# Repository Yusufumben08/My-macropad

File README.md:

# My-macropad

first electronics project. I found this last second so i couldnt do much more than this because of the time constraint. Made in 5~ hours. I have access to a 3d printer and will print the case myself (possibly iterating on it to make it look better.)

Parts list / BOM: <br>
*Seeed XIAO RP2040 1x505TL [link](https://www.robotsepeti.com/xiao-rp2040-rpi-tabanli-gelistirme-karti?srsltid=AfmBOoo-r4c254mQOyLpYBEuEKQ4UjQO35CaTtn0vQ_AmNtM1wtQWy1J) <br>
*9x MX-Style switches 450-500TL (this was the only listing i found and it sells 10 so price is approximated.) [link](https://www.hepsiburada.com/cherry-mx-mekanik-klavye-blue-switch-yedek-tus-10-adet-pm-HB00000TWEHL). <br>
*EC11 Rotary encoder 1x32TL [link](https://www.robolinkmarket.com/rotary-encoder-ec11-switch-20mm?srsltid=AfmBOople9BYicgfWd3Uo1zGUX4RngiUt7oklPvnFAZ-H85KapwNfm2Q)<br>
*9x Blank DSA keycaps (wasnt able to find a listing on this one, i can source it myself when i find it.)<br>
*9x SK6812 MINI-E LEDs 35TL~ (same with the switches, the only listing i could find sold 10 so approximate price.) [link](https://tr.aliexpress.com/item/1005005248164351.html) <br>
*9x Through-hole 1N4148 Diodes 9x0,41 ,3,67TL [link](https://www.direnc.net/1n4148-diyot-mic)<br>

Total: 1025TL~ = 24~ US dollars

Schematic:

PCB Image:

Model of assembled form:

Case Parts:

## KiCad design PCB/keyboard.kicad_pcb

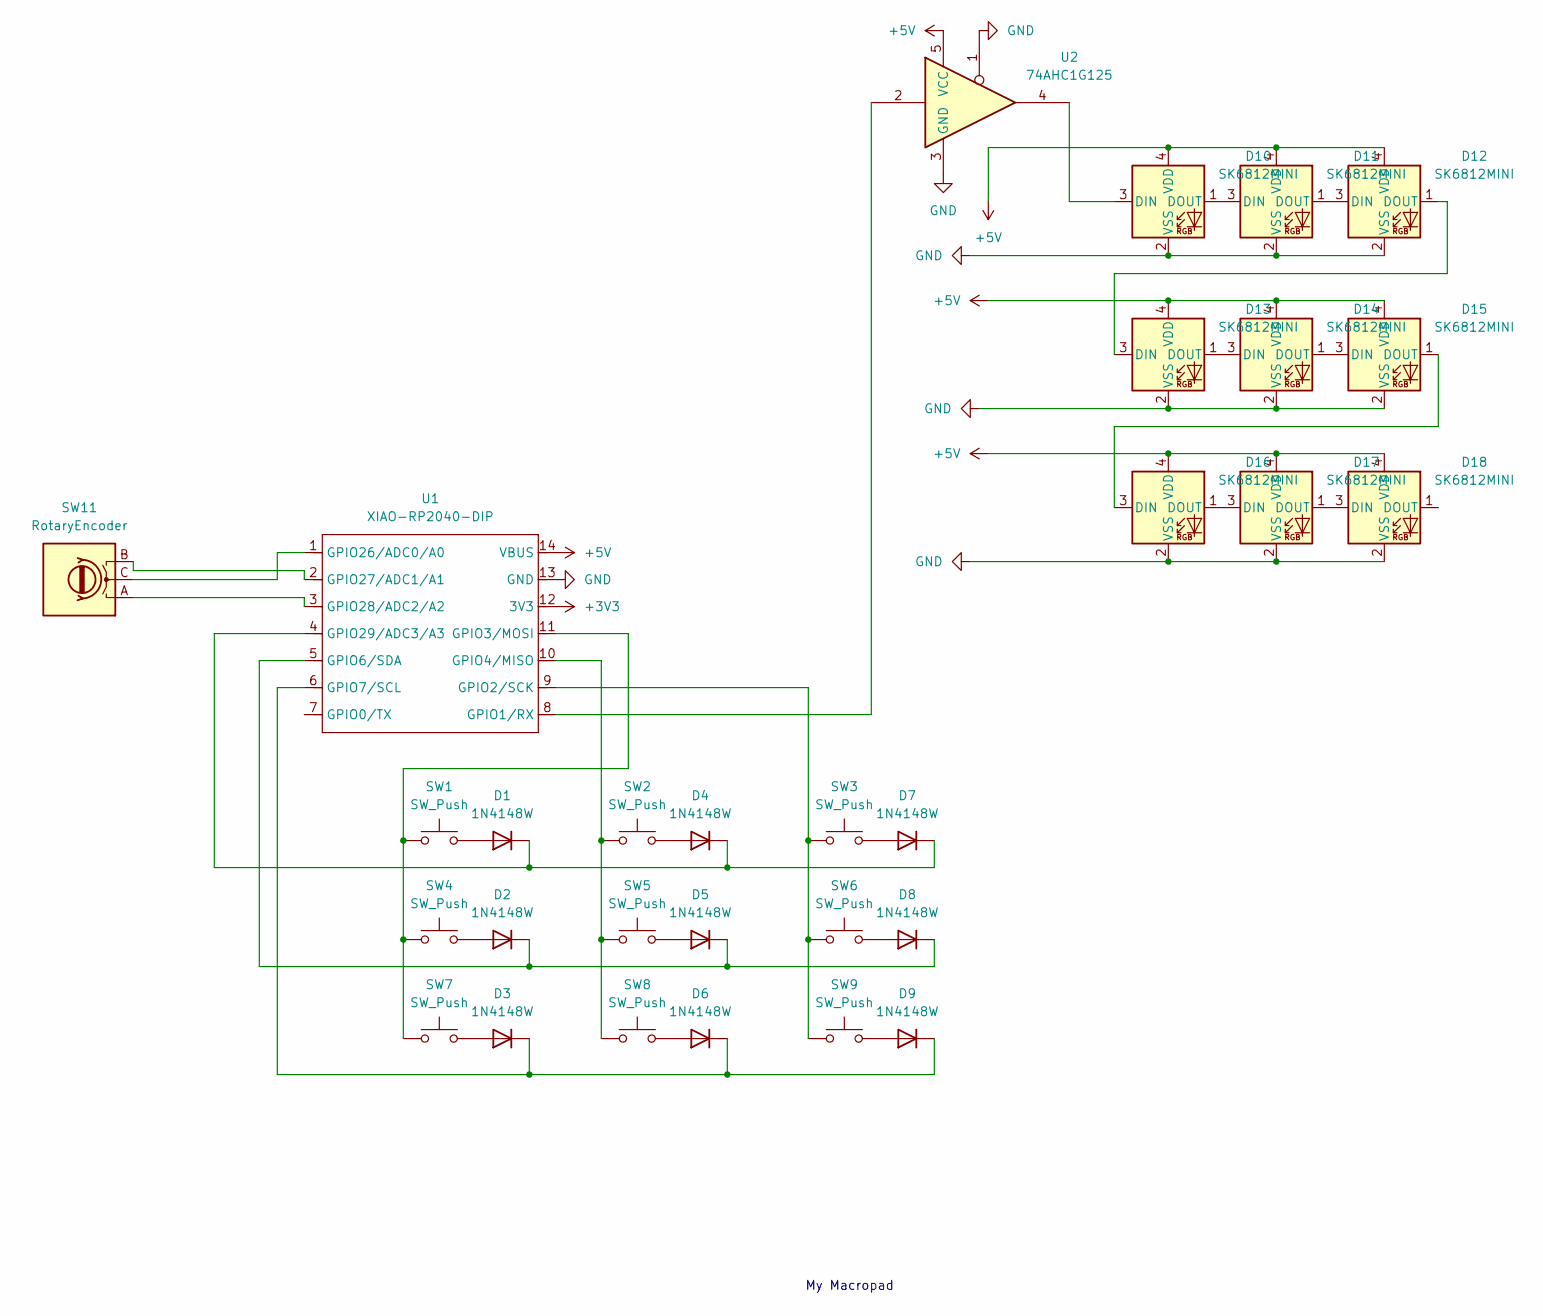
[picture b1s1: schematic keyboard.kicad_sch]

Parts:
D1, D2, D3, D4, D5, D6, D7, D8, D9: 1N4148W; D_SOD-123
D10, D11, D12, D13, D14, D15, D16, D17, D18: SK6812MINI; LED_SK6812MINI_PLCC4_3.5x3.5mm_P1.75mm
SW1, SW2, SW3, SW4, SW5, SW6, SW7, SW8, SW9: SW_Push; SW_Cherry_MX_1.00u_PCB
SW11: RotaryEncoder; RotaryEncoder_Alps_EC11E-Switch_Vertical_H20mm
U1: XIAO-RP2040-DIP
U2: 74AHC1G125; SOT95P280X140-5N

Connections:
+3V3: U1.12 (3V3)
+5V: D10.4 (VDD), D11.4 (VDD), D12.4 (VDD), D13.4 (VDD), D14.4 (VDD), D15.4 (VDD), D16.4 (VDD), D17.4 (VDD), D18.4 (VDD), U1.14 (VBUS), U2.5 (VCC)
GND: D10.2 (VSS), D11.2 (VSS), D12.2 (VSS), D13.2 (VSS), D14.2 (VSS), D15.2 (VSS), D16.2 (VSS), D17.2 (VSS), D18.2 (VSS), U1.13 (GND), U2.1, U2.3 (GND)
unnamed: D1.2 (A), SW1.2
unnamed: D1.1 (K), D4.1 (K), D7.1 (K), U1.4 (GPIO29/ADC3/A3)
unnamed: D2.2 (A), SW4.2
unnamed: D2.1 (K), D5.1 (K), D8.1 (K), U1.5 (GPIO6/SDA)
unnamed: D3.2 (A), SW7.2
unnamed: D3.1 (K), D6.1 (K), D9.1 (K), U1.6 (GPIO7/SCL)
unnamed: D4.2 (A), SW2.2
unnamed: D5.2 (A), SW5.2
unnamed: D6.2 (A), SW8.2
unnamed: D7.2 (A), SW3.2
unnamed: D8.2 (A), SW6.2
unnamed: D9.2 (A), SW9.2
unnamed: D10.3 (DIN), U2.4
unnamed: D10.1 (DOUT), D11.3 (DIN)
unnamed: D11.1 (DOUT), D12.3 (DIN)
unnamed: D12.1 (DOUT), D13.3 (DIN)
unnamed: D13.1 (DOUT), D14.3 (DIN)
unnamed: D14.1 (DOUT), D15.3 (DIN)
unnamed: D15.1 (DOUT), D16.3 (DIN)
unnamed: D16.1 (DOUT), D17.3 (DIN)
unnamed: D17.1 (DOUT), D18.3 (DIN)
unnamed: U1.8 (GPIO1/RX), U2.2
unnamed: SW3.1, SW6.1, SW9.1, U1.9 (GPIO2/SCK)
unnamed: SW1.1, SW4.1, SW7.1, U1.11 (GPIO3/MOSI)
unnamed: SW2.1, SW5.1, SW8.1, U1.10 (GPIO4/MISO)
unnamed: SW11.C, U1.1 (GPIO26/ADC0/A0)
unnamed: SW11.B, U1.2 (GPIO27/ADC1/A1)
unnamed: SW11.A, U1.3 (GPIO28/ADC2/A2)

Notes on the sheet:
My Macropad

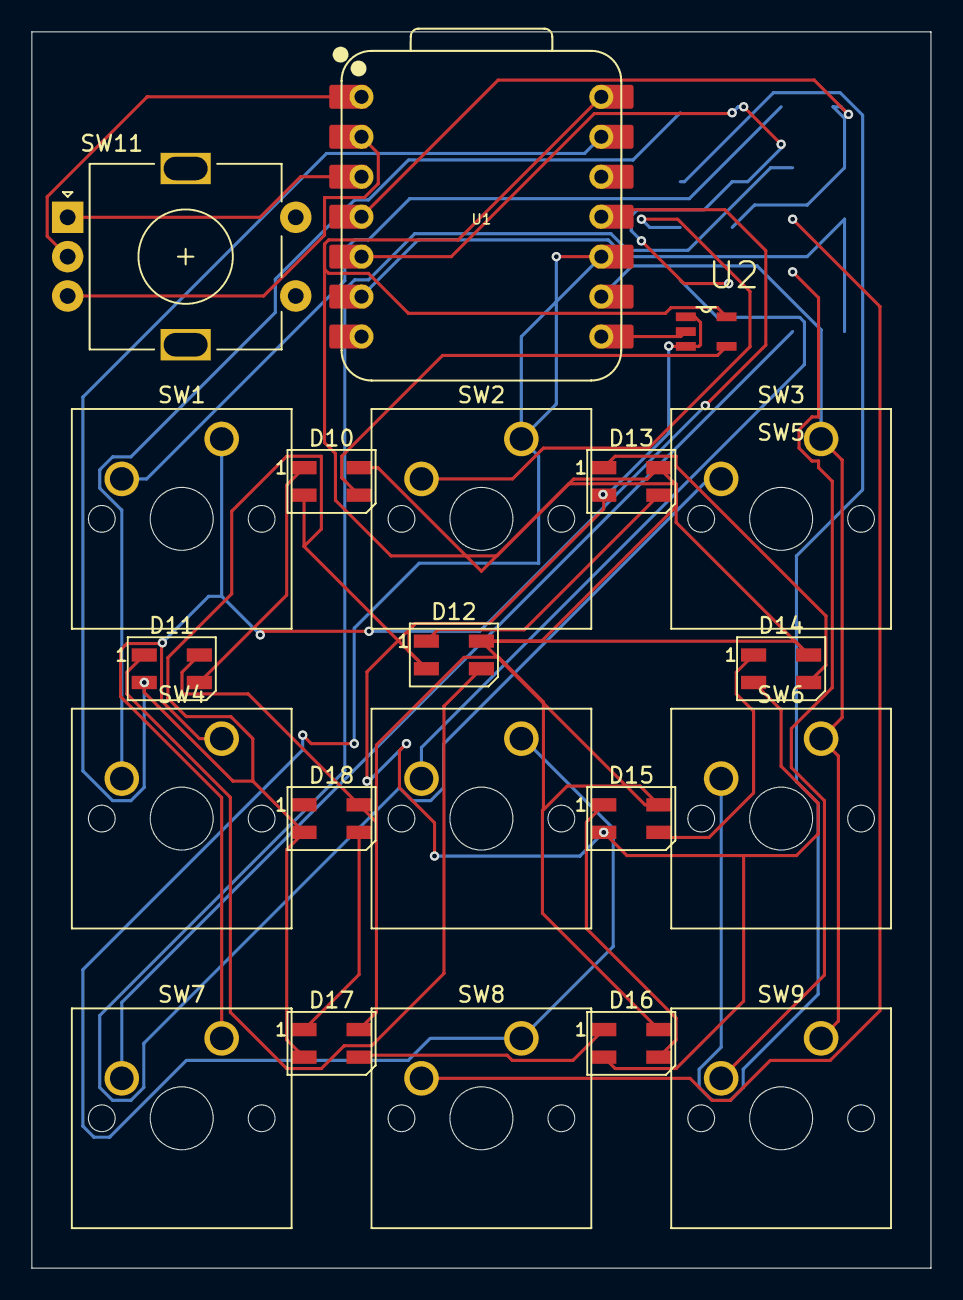
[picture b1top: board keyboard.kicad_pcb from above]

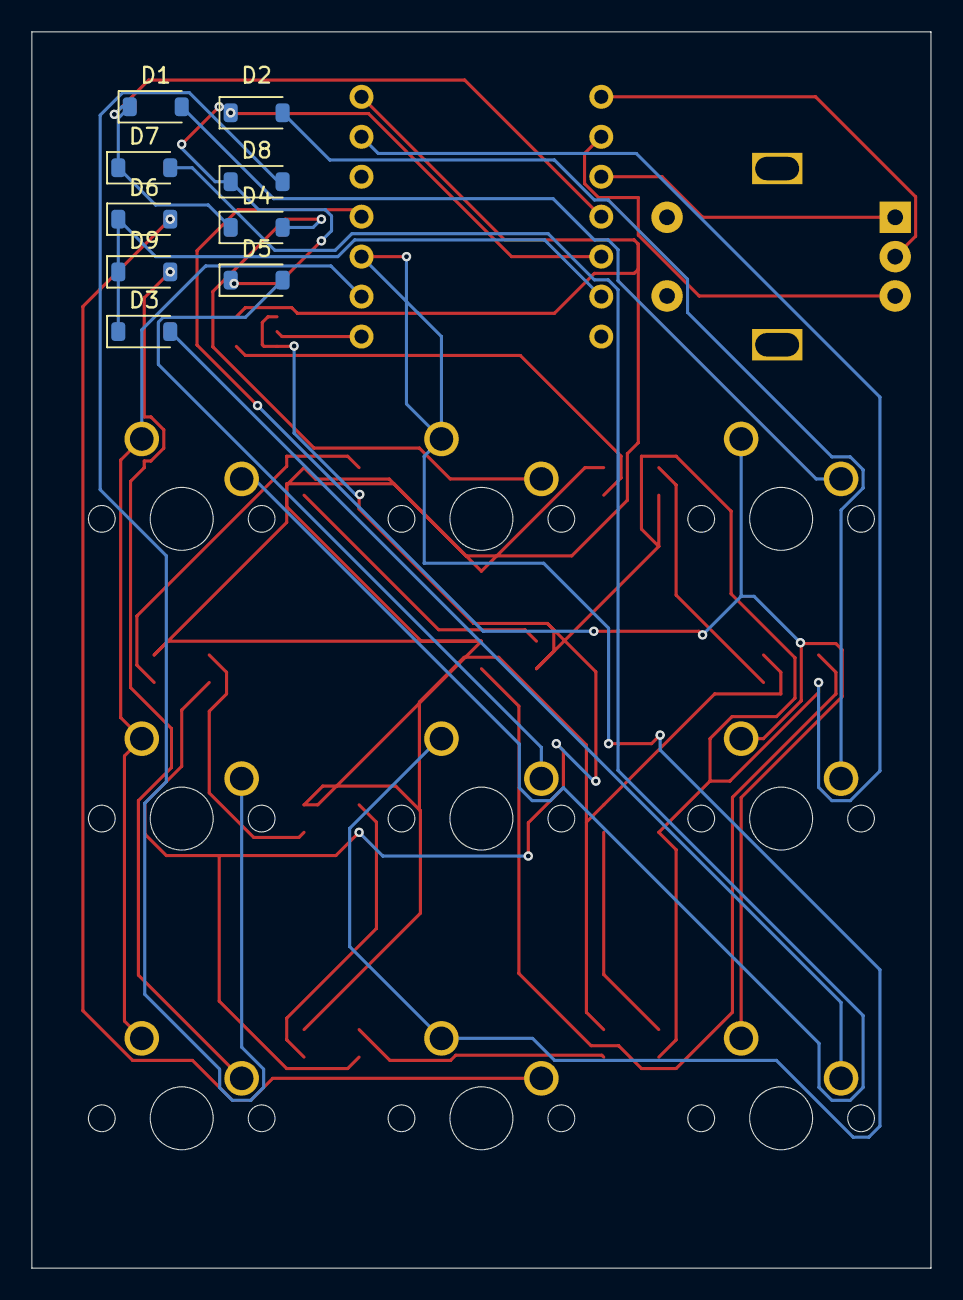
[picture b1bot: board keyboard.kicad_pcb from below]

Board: 2 copper layers, 57.2 x 78.6 mm, 30 parts (9 on the bottom side), 30 nets.

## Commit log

2025-12-04 Create none
2025-12-05 Update README.md
    update
2025-12-05 pcb image
2025-12-05 edit readme
2025-12-05 final?
2025-12-05 image
2025-12-05 spacing
    spacing
2025-12-05 msg
    Updated README to include collaboration details and project timeline.
2025-12-05 Update README.md
    parts
2025-12-05 Update README.md
    fix
2025-12-05 Update README.md
    final
2025-12-06 Update README.md
    unfinished model :(
2025-12-08 Update README.md
    bom
2025-12-08 Update README.md
    total
